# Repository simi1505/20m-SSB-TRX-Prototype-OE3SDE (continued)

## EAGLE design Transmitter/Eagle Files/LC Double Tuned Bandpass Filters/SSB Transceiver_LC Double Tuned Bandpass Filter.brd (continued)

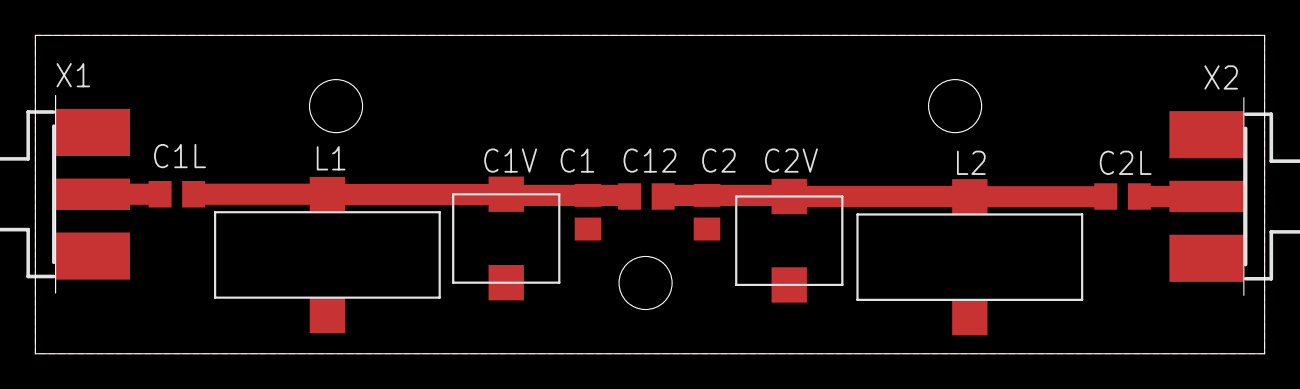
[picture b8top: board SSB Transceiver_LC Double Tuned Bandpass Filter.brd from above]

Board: 2 copper layers, 69.5 x 18.0 mm, 11 parts (0 on the bottom side), 5 nets.
